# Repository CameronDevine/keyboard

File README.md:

#The Emoji Keyboard#

##FAQ##

If you run into any problems using the keyboard normally, please see the FAQ located [here](FAQ.md).

##Reprograming##

###Drivers###

This keyboard is an Adafruit Trinket 5V with three buttons and missing a couple of LEDs. If you would like to try to reprogram the board, the webpage [here](https://learn.adafruit.com/introducing-trinket/introduction) will guide you through installing the necessary drivers. And give a general introduction to programming the board.

###Bootloader###

Once the correct drivers are installed, and you are ready to program the board, the bootloader needs to be activated. On the Adafruit Trinket there is a button supplied for this purpose. On the keyboard there are two ways this can be done.

####Method 1####

One way to activate the bootloader is to unplug the USB cable and plug it back in. This will start the bootloader for a couple seconds before the board enters its keyboard mode.

####Method 2####

The other method is to short the reset (Rst) and ground (Gnd) pins. This second method has the exact same effect as the reset button on the Trinket.

###Libraries###

Two libraries are needed for the keyboard code to run. One is the built in EEPROM library and the other is the Trinket Keyboard library located [here](https://github.com/adafruit/Adafruit-Trinket-USB/archive/master.zip).

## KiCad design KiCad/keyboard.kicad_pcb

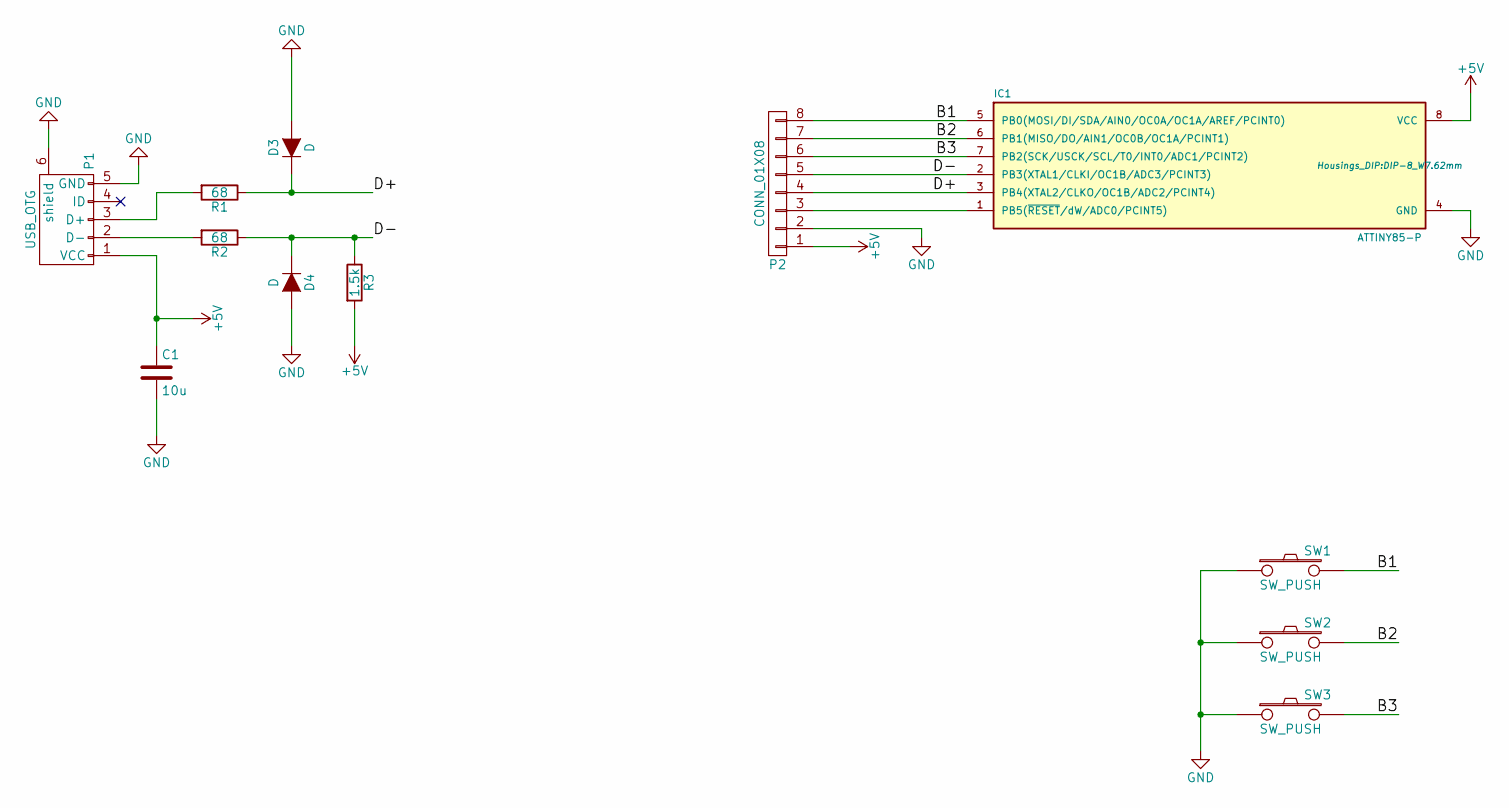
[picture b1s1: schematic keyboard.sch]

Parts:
C1: 10u; C_Radial_D5_L11_P2
D3, D4: D; Diode_DO-35_SOD27_Horizontal_RM10
IC1: ATTINY85-P; DIP-8_W7.62mm
P1: USB_OTG; USB
P2: CONN_01X08; Pin_Header_Straight_1x08
R1, R2: 68; Resistor_Horizontal_RM10mm
R3: 1.5k; Resistor_Horizontal_RM10mm
SW1, SW2, SW3: SW_PUSH; SW_PUSH_SMALL

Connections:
+5V: C1.1, IC1.8 (VCC), P1.1 (VCC), P2.1, R3.2
/B1: IC1.5 (PB0(MOSI/DI/SDA/AIN0/OC0A/OC1A/AREF/PCI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), P2.8, SW1.2
/B2: IC1.6 (PB1(MISO/DO/AIN1/OC0B/OC1A/PCINT1)), P2.7, SW2.2
/B3: IC1.7 (PB2(SCK/USCK/SCL/T0/INT0/ADC1/PCINT2)), P2.6, SW3.2
/D+: D3.1 (K), IC1.3 (PB4(XTAL2/CLKO/OC1B/ADC2/PCINT4)), P2.4, R1.1
/D-: D4.1 (K), IC1.2 (PB3(XTAL1/CLKI/OC1B/ADC3/PCINT3)), P2.5, R2.1, R3.1
GND: C1.2, D3.2 (A), D4.2 (A), IC1.4 (GND), P1.5 (GND), P1.6 (shield), P2.2, SW1.1, SW2.1, SW3.1
unnamed: IC1.1 (PB5(~RESET~/dW/ADC0/PCINT5)), P2.3
unnamed: P1.2 (D-), R2.2
unnamed: P1.3 (D+), R1.2

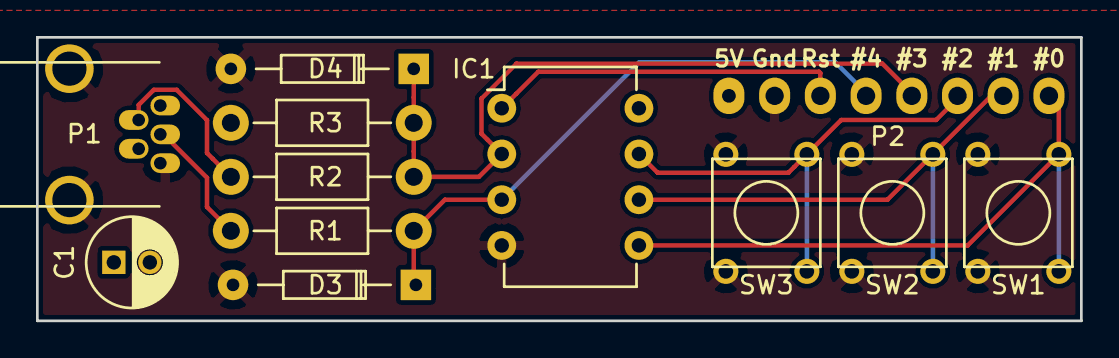
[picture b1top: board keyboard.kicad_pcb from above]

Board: 2 copper layers, 58.0 x 15.8 mm, 12 parts (0 on the bottom side), 10 nets.

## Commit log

2016-03-30 added readme
2016-03-30 added more info to readme
2016-03-30 added parts list
2016-03-30 adding KiCad PCB files.
2016-03-30 added links to readme
2016-03-30 adding arduino code
2016-03-30 added FAQ
2016-03-30 fixed spelling errors
